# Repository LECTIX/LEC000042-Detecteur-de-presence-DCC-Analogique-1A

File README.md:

# LEC000042-Detecteur-de-presence-DCC-Analogique-1A
Fichiers sources pour le produit LEC000042

## Description du produit

### DCC (Digital)

En DCC, le détecteur d’occupation LEC000042 permet de détecter l’occupation d’un tronçon de voie et de déclencher de nombreux automatismes ou systèmes.
- Détecte tous les trains dans les **2 sens de marche**.
- Seuil de détection **ultrasensible et réglable**.
- **Relais double inverseur** pour y brancher n'importe quel système.
- Temporisation à la désactivation pour **éviter des réactivations intempestives**.
- **Possibilité de forcer** l'activation du relais via un bornier dédié.

### Analogique

Le détecteur d’occupation LEC000042 permet de détecter l’occupation d’un tronçon de voie et de déclencher de nombreux automatismes ou systèmes.
- Détecte tous les trains dans **1 seul sens de marche, à partir de 6 V**.
- Seuil de détection **ultrasensible et réglable**.
- **Relais double inverseur** pour y brancher n'importe quel système.
- Temporisation à la désactivation pour **éviter des réactivations intempestives**.
- **Possibilité de forcer** l'activation du relais via un bornier dédié.

## Utiliser les fichiers sources pour fabriquer le produit

Il n'est **pas nécessaire de savoir souder ou d'être bon en électronique** pour se procurer ce produit. Grâce aux fichiers sources publiés ici, vous pouvez être en mesure de faire fabriquer ce produit par un sous traitant.

### Faire fabriquer chez un sous traitant

Il est aujourd'hui possible de faire fabriquer à moindre cout des cartes électroniques. Nous recommendons [JLCPCB](https://jlcpcb.com/) si vous voulez aller au moins cher. Si vous préférez un acteur européen, [eurocircuits](https://www.eurocircuits.com/) est un des acteurs reconnus.

1. Télécherger les sources de ce produit en cliquant sur le bouton `Code`, puis `Download ZIP`.
1. Décompresser le dossier.
1. Les fichiers pour la fabrication se trouvent dans le répertoire `hardware/prod`.
1. Se connecter sur [https://cart.jlcpcb.com/quote](https://cart.jlcpcb.com/quote)
1. Cliquer sur le bouton `Add gerber file` et sélectionner le fichier `gerbers.zip`.
1. Sélectionnez la quantité de cartes que vous souhaitez dans le champs `PCB Qty`.
1. Laisser toutes les autres options par défaut, puis cliquez sur le toggle switch en face de `PCB Assembly`, et enfin sur le bouton `confirm`.
1. Une preview de la carte électronique sans les composants doit apparaitre. Cliquez sur `NEXT`.
1. Cliquez sur le bouton `Add BOM File`, puis sélectionnez le fichier `bom.csv`
1. Cliquez sur le bouton `Add CPL File`, puis sélectionnez le fichier `pos.csv`
1. **Vérifier que tous les composants sont en stock** et bien sélectionnés, puis cliquez sur `NEXT`.
1. Une preview de la carte avec ses composants apparait. Continuer le chemin en cliquant sur `NEXT`.
1. Le prix final apparait. Sélectionnez la catégorie du produit, puis cliquez sur `SAVE TO CART`.
1. Une fois sauvegardé dans votre panier, vous pouvez valider votre commande et choisir le moyen d'acheminement. Afin de ne pas avoir à se préoccuper des frais de douane, nous vous conseillons de choisir une méthode d'expédition DDP.

Vous receverez vos cartes sous 1 à 3 semaines. 

**Nous ne sommes en aucun cas responsables des cartes qui arriveraient défectueuses ou non fonctionnelles.**

### Modifications des fichiers sources

Installez kicad 6 (ou version supérieure), et ouvrez le fichier LEC000042.kicad_pro

### Regénérer les fichiers gerber, BOM, et position (Optionnel)

Peut se faire simplement en utilisant kikit :

```
cd hardware
docker run --rm -w /kikit -v $PWD:/kikit yaqwsx/kikit kikit fab jlcpcb --assembly --no-drc --schematic LEC000042.kicad_sch --field LCSC --corrections JLCPCB_CORRECTION --nametemplate LEC000042_{} LEC000042.kicad_pcb prod/

```
## Notices

### DCC

[Manuel FR](docs/dcc/manual_fr.pdf)

[Manuel EN](docs/dcc/manual_en.pdf)

### Analogique

[Manuel FR](docs/analogique/manual_fr.pdf)

## License
Tous nos fichiers sont plubliés sous la license CERN Open Hardware Licence Version 2 - Strongly Reciprocal

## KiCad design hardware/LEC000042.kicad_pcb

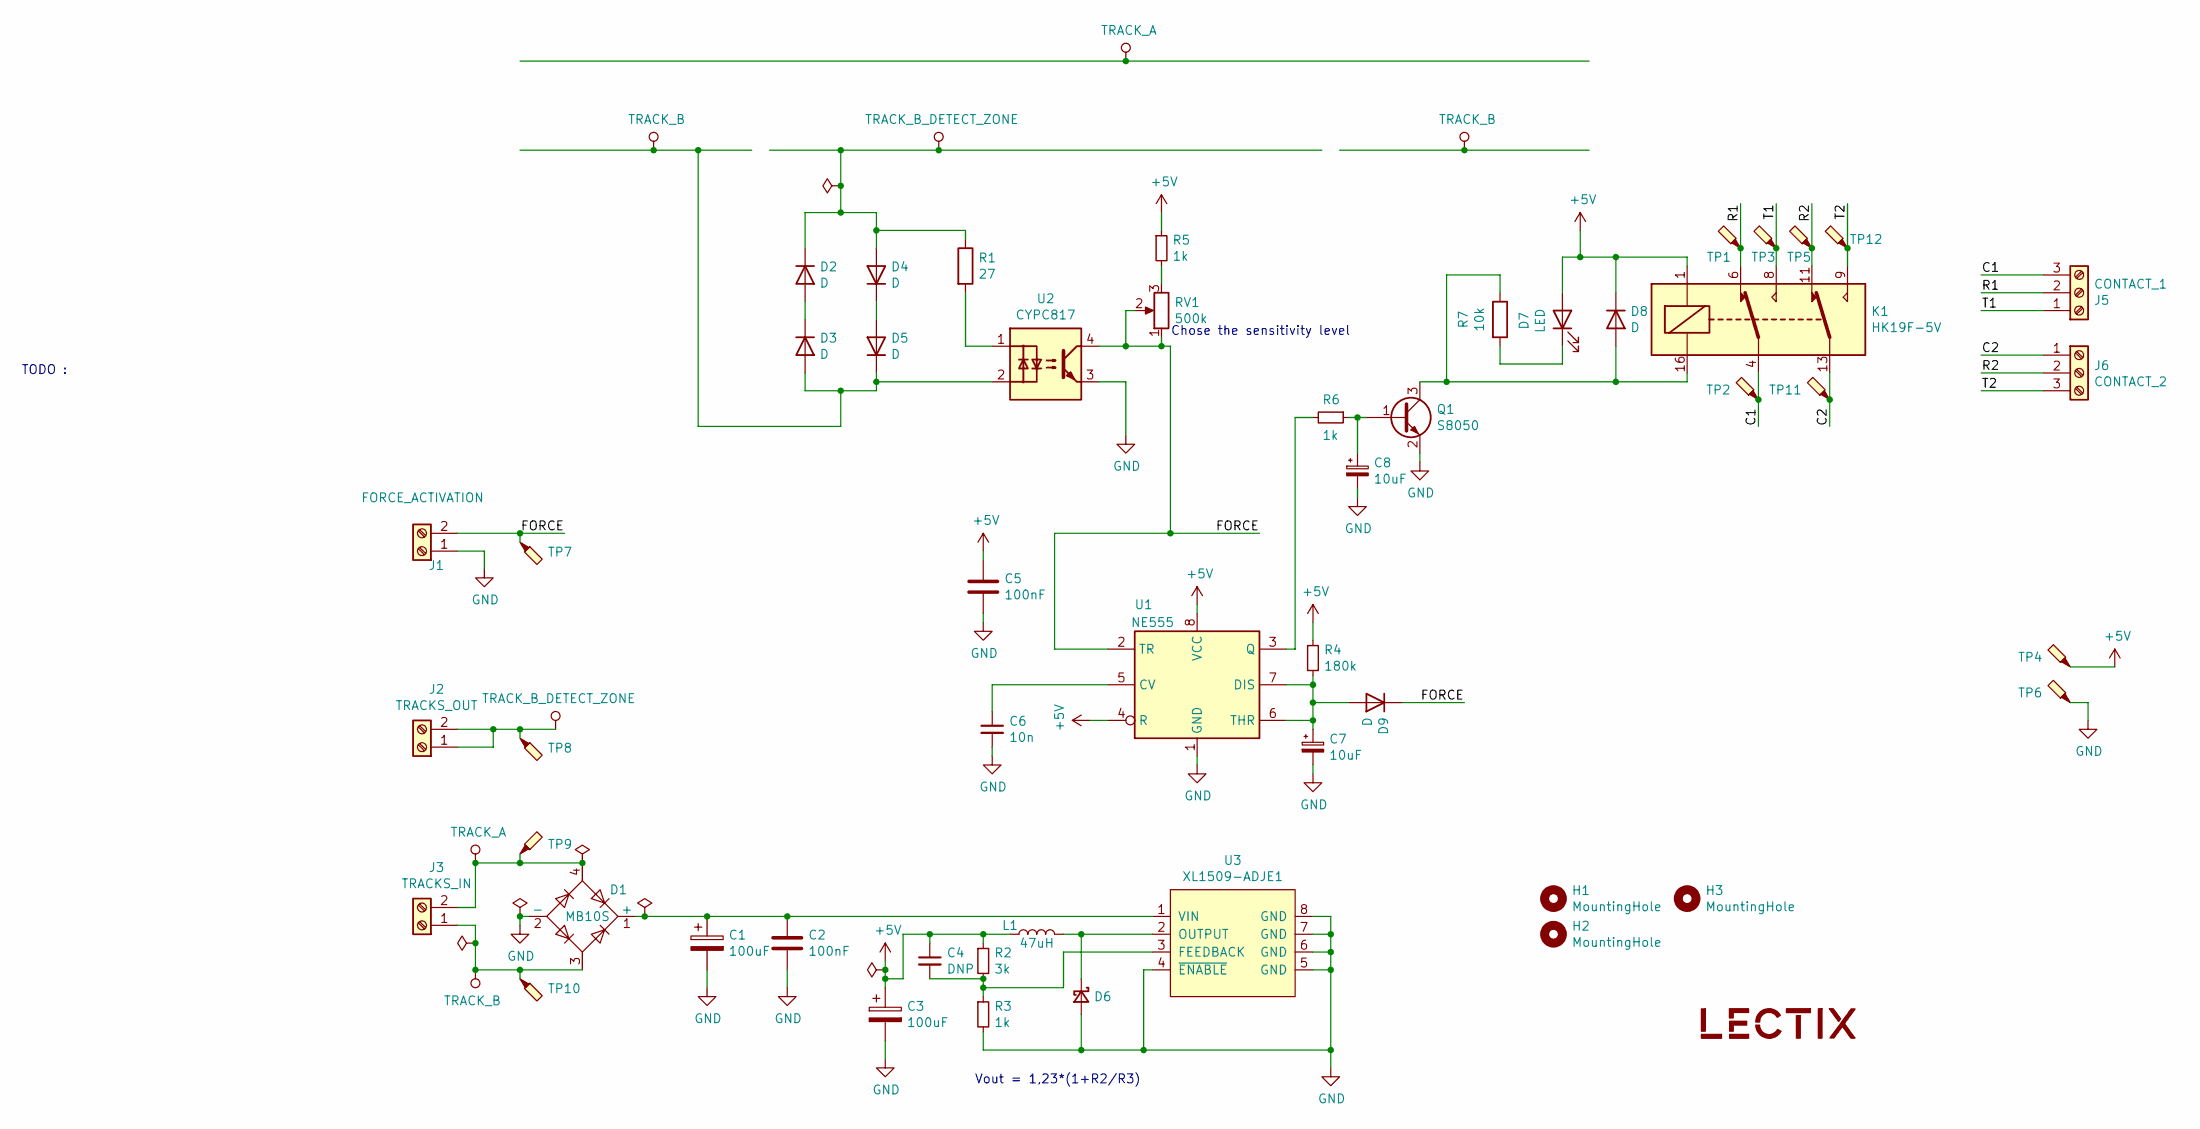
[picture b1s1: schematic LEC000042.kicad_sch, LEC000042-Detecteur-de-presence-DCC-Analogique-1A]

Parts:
C1, C3: 100uF; CP_Elec_6.3x5.8; MPN VZT101M1VTR-0606; LCSC C249982
C2, C5: 100nF; C_0603_1608Metric; MPN CC0603KRX7R9BB104; LCSC C14663
C4: DNP; C_0603_1608Metric; MPN DNP; LCSC DNP
C6: 10n; C_0603_1608Metric; MPN 0603B103K500NT; LCSC C57112
C7, C8: 10uF; CP_EIA-3216-18_Kemet-A; MPN TAJA106K016RNJ; LCSC C7171
D1: MB10S; TO-269AA; MPN MB10S; LCSC C2488
D2, D3, D4, D5, D8, D9: D; D_SMA; MPN M7; LCSC C95872
D6: D_Schottky_Small; D_SMA; MPN SS54; LCSC C22452
D7: LED; LED_0603_1608Metric; MPN 19-217/GHC-YR1S2/3T; LCSC C72043
H1, H2, H3: MountingHole; MountingHole_3.2mm_M3; MPN DNP; LCSC DNP
J1: FORCE_ACTIVATION; TerminalBlock_bornier-2_P5.08mm-blue; MPN DB301V-5.0-2P-BU-P; LCSC C430621
J2: TRACKS_OUT; TerminalBlock_bornier-2_P5.08mm-blue; MPN DB301V-5.0-2P-BU-P; LCSC C430621
J3: TRACKS_IN; TerminalBlock_bornier-2_P5.08mm-green; MPN DB126V-5.0-2P-GN; LCSC C395849
J5: CONTACT_1; TerminalBlock_bornier-3_P5.08mm-blue; MPN DB301V-5.0-3P-BU-P; LCSC C430620
J6: CONTACT_2; TerminalBlock_bornier-3_P5.08mm-blue; MPN DB301V-5.0-3P-BU-P; LCSC C430620
K1: HK19F-5V; Relay_DPDT_HK19F; MPN HK19F-DC5V-SHG-Y; LCSC C54512
L1: 47uH; L_12x12mm_H6mm; MPN SWRB1204S-470MT; LCSC C169398
LOGO1: logo_lectix_25mm; Logo_10mm; MPN DNP; LCSC DNP
Q1: S8050; SOT-23; MPN S8050; LCSC C2146
R1: 27; R_0603_1608Metric; MPN 0603WAF270JT5E; LCSC C25190
R2: 3k; R_0603_1608Metric; MPN 0603WAF3001T5E; LCSC C4211
R3, R5, R6: 1k; R_0603_1608Metric; MPN 0603WAF1001T5E; LCSC C21190
R4: 180k; R_0603_1608Metric; MPN 0603WAF1803T5E; LCSC C22827
R7: 10k; R_0603_1608Metric; MPN 0603WAF1002T5E; LCSC C25804
RV1: 500k; BOURNS-3362P_pot; MPN 3362P-1-504; LCSC C125021
TP1, TP2, TP3, TP4, TP5, TP6, TP7, TP8, TP9, TP10, TP11, TP12: TestPoint_Probe; TestPoint_Pad_D1.5mm; MPN DNP; LCSC DNP
U1: NE555; SOIC-8_3.9x4.9mm_P1.27mm; MPN NE555; LCSC C7593
U2: CYPC817; SMDIP-4_W9.53mm_Clearance8mm; MPN CYPC817(B-TP2); LCSC C385060
U3: XL1509-ADJE1; SOP-8_3.76x4.96mm_P1.27mm; MPN XL1509-ADJE1; LCSC C74192

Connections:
+5V: C3.1, C4.1, C5.1, D7.2 (A), D8.1 (K), K1.1, L1.1, R2.1, R4.1, R5.1, TP4.1, U1.4 (R), U1.8 (VCC)
/C1: J5.3, K1.4, TP2.1
/C2: J6.1, K1.13, TP11.1
/FORCE: D9.1 (K), J1.2, RV1.1, RV1.2, TP7.1, U1.2 (TR), U2.4
/R1: J5.2, K1.6, TP1.1
/R2: J6.2, K1.11, TP5.1
/T1: J5.1, K1.8, TP3.1
/T2: J6.3, K1.9, TP12.1
GND: C1.2, C2.2, C3.2, C5.2, C6.2, C7.2, C8.2, D1.2 (-), D6.2 (A), J1.1, Q1.2 (E), R3.2, TP6.1, U1.1 (GND), U2.3, U3.4 (~ENABLE), U3.5 (GND), U3.6 (GND), U3.7 (GND), U3.8 (GND)
unnamed: C1.1, C2.1, D1.1 (+), U3.1 (VIN)
unnamed: C4.2, R2.2, R3.1, U3.3 (FEEDBACK)
unnamed: C6.1, U1.5 (CV)
unnamed: C7.1, D9.2 (A), R4.2, U1.6 (THR), U1.7 (DIS)
unnamed: C8.1, Q1.1 (B), R6.1
unnamed: D2.2 (A), D3.1 (K)
unnamed: D4.1 (K), D5.2 (A)
unnamed: D6.1 (K), L1.2, U3.2 (OUTPUT)
unnamed: D7.1 (K), R7.2
unnamed: D8.2 (A), K1.16, Q1.3 (C), R7.1
unnamed: R1.2, U2.1
unnamed: R5.2, RV1.3
unnamed: R6.2, U1.3 (Q)
TRACK_A: D1.4, J3.2, TP9.1
TRACK_B: D1.3, D3.2 (A), D5.1 (K), J3.1, TP10.1, U2.2
TRACK_B_DETECT_ZONE: D2.1 (K), D4.2 (A), J2.1, J2.2, R1.1, TP8.1

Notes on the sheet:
TODO :
Vout = 1,23*(1+R2/R3)
Chose the sensitivity level

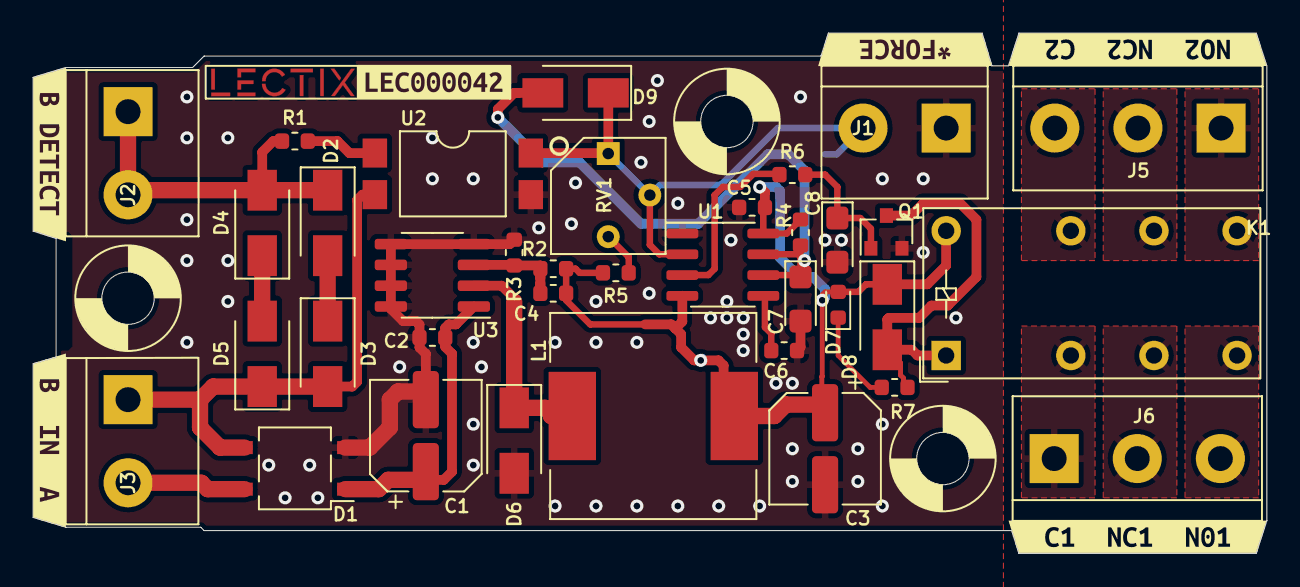
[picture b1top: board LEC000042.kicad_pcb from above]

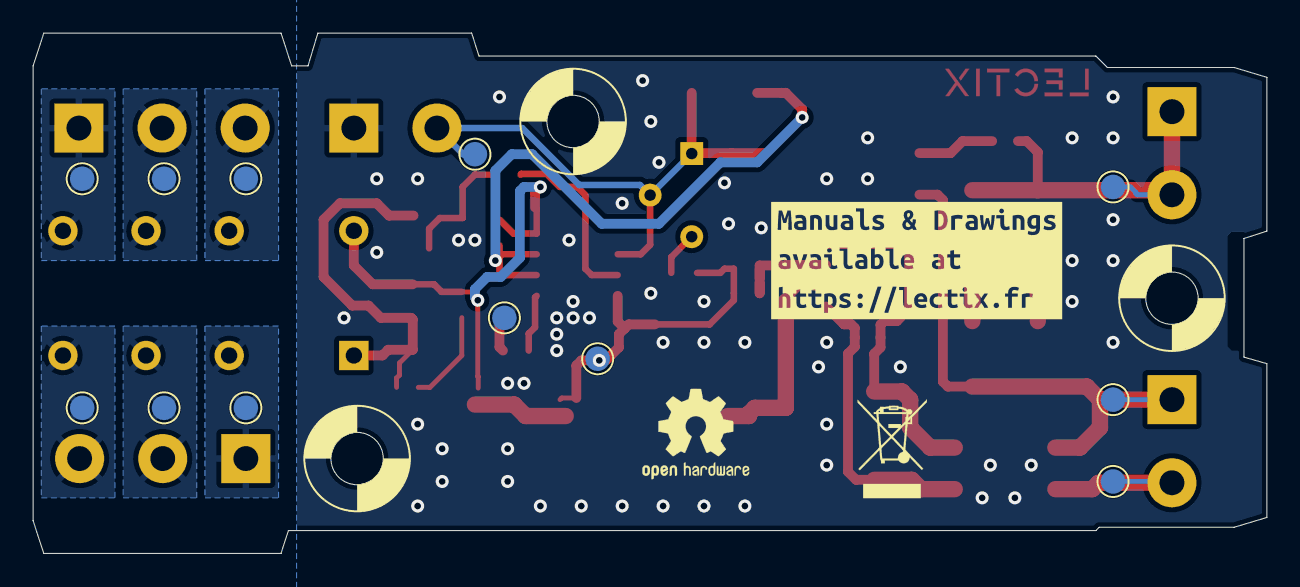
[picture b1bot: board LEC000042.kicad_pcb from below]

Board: 2 copper layers, 75.4 x 31.8 mm, 59 parts (13 on the bottom side), 25 nets.

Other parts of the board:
kibuzzard-624D4A0B: G***; kibuzzard-624D4A0B
kibuzzard-624D4A7D: G***; kibuzzard-624D4A7D
kibuzzard-624D4ACF: G***; kibuzzard-624D4ACF
kibuzzard-624D4AF8: G***; kibuzzard-624D4AF8
kibuzzard-624D4BCC: G***; kibuzzard-624D4BCC
kibuzzard-624D4BDE: G***; kibuzzard-624D4BDE
kibuzzard-624D5053: G***; kibuzzard-624D5053

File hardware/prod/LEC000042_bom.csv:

Comment,Designator,Footprint,LCSC
100uF,"C1,C3",0_capacitors:CP_Elec_6.3x5.8,C249982
100nF,"C2,C5",Capacitor_SMD:C_0603_1608Metric,C14663
10n,C6,Capacitor_SMD:C_0603_1608Metric,C57112
10uF,"C7,C8",Capacitor_Tantalum_SMD:CP_EIA-3216-18_Kemet-A,C7171
MB10S,D1,Package_TO_SOT_SMD:TO-269AA,C2488
D,"D2,D3,D4,D5,D8,D9",Diode_SMD:D_SMA,C95872
D_Schottky_Small,D6,Diode_SMD:D_SMA,C22452
LED,D7,LED_SMD:LED_0603_1608Metric,C72043
FORCE_ACTIVATION,J1,0_connectors:TerminalBlock_bornier-2_P5.08mm-blue,C430621
TRACKS_OUT,J2,0_connectors:TerminalBlock_bornier-2_P5.08mm-blue,C430621
TRACKS_IN,J3,0_connectors:TerminalBlock_bornier-2_P5.08mm-green,C395849
CONTACT_1,J5,0_connectors:TerminalBlock_bornier-3_P5.08mm-blue,C430620
CONTACT_2,J6,0_connectors:TerminalBlock_bornier-3_P5.08mm-blue,C430620
HK19F-5V,K1,0_relays:Relay_DPDT_HK19F,C54512
47uH,L1,Inductor_SMD:L_12x12mm_H6mm,C169398
S8050,Q1,Package_TO_SOT_SMD:SOT-23,C2146
27,R1,Resistor_SMD:R_0603_1608Metric,C25190
3k,R2,Resistor_SMD:R_0603_1608Metric,C4211
1k,"R3,R5,R6",Resistor_SMD:R_0603_1608Metric,C21190
180k,R4,Resistor_SMD:R_0603_1608Metric,C22827
10k,R7,Resistor_SMD:R_0603_1608Metric,C25804
500k,RV1,0_potentiometers:BOURNS-3362P_pot,C125021
NE555,U1,Package_SO:SOIC-8_3.9x4.9mm_P1.27mm,C7593
CYPC817,U2,Package_DIP:SMDIP-4_W9.53mm_Clearance8mm,C385060
XL1509-ADJE1,U3,Package_SO:SOP-8_3.76x4.96mm_P1.27mm,C74192

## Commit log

2023-03-26 Add product manuals$
2023-03-26 Add source files
2023-03-26 Add prod files
2023-03-26 Add pdf schematic file
2023-03-26 Add demo video

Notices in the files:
hardware/LEC000042.kicad_sch:
CERN-OHL-S-2.0 license
